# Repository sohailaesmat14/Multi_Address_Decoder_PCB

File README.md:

# Multi Address Decoder PCB

## Description

The Multi-Address Decoder PCB is a versatile printed circuit board designed by Sohaila Esmat using Eagle PCB design software. It serves as a crucial component in digital electronics systems, facilitating the decoding of multiple address lines into individual select signals.

## Features

- **Address Decoding:** Efficiently decodes multiple address lines into select signals.
- **Versatile Design:** Can be integrated into various digital electronics projects requiring address decoding functionality.
- **Customizable:** The design is open for customization and adaptation to specific project requirements.
- **Eagle PCB Design:** Designed using Eagle PCB design software, ensuring reliability and compatibility with industry-standard workflows.

## Design Files

- **Schematic:** The schematic diagram of the Multi-Address Decoder PCB is provided in Eagle `.sch` format.
- **PCB Layout:** The PCB layout design files are available in Eagle `.brd` format.
- **Gerber Files:** Gerber files for manufacturing the PCB are included for easy fabrication.
## PCB Design:

## Usage

1. **Customization:** Modify the design to suit your specific project requirements, such as the number of address lines and select outputs.
2. **Fabrication:** Use the provided Gerber files to manufacture the PCB according to the design specifications.
3. **Integration:** Incorporate the Multi-Address Decoder PCB into your digital electronics project, connecting address lines and select outputs as needed.
4. **Testing:** Validate the functionality of the PCB by testing its address decoding capabilities in your system.

## Author

- **Sohaila Esmat:** [LinkedIn](https://www.linkedin.com/in/sohailaesmat/)

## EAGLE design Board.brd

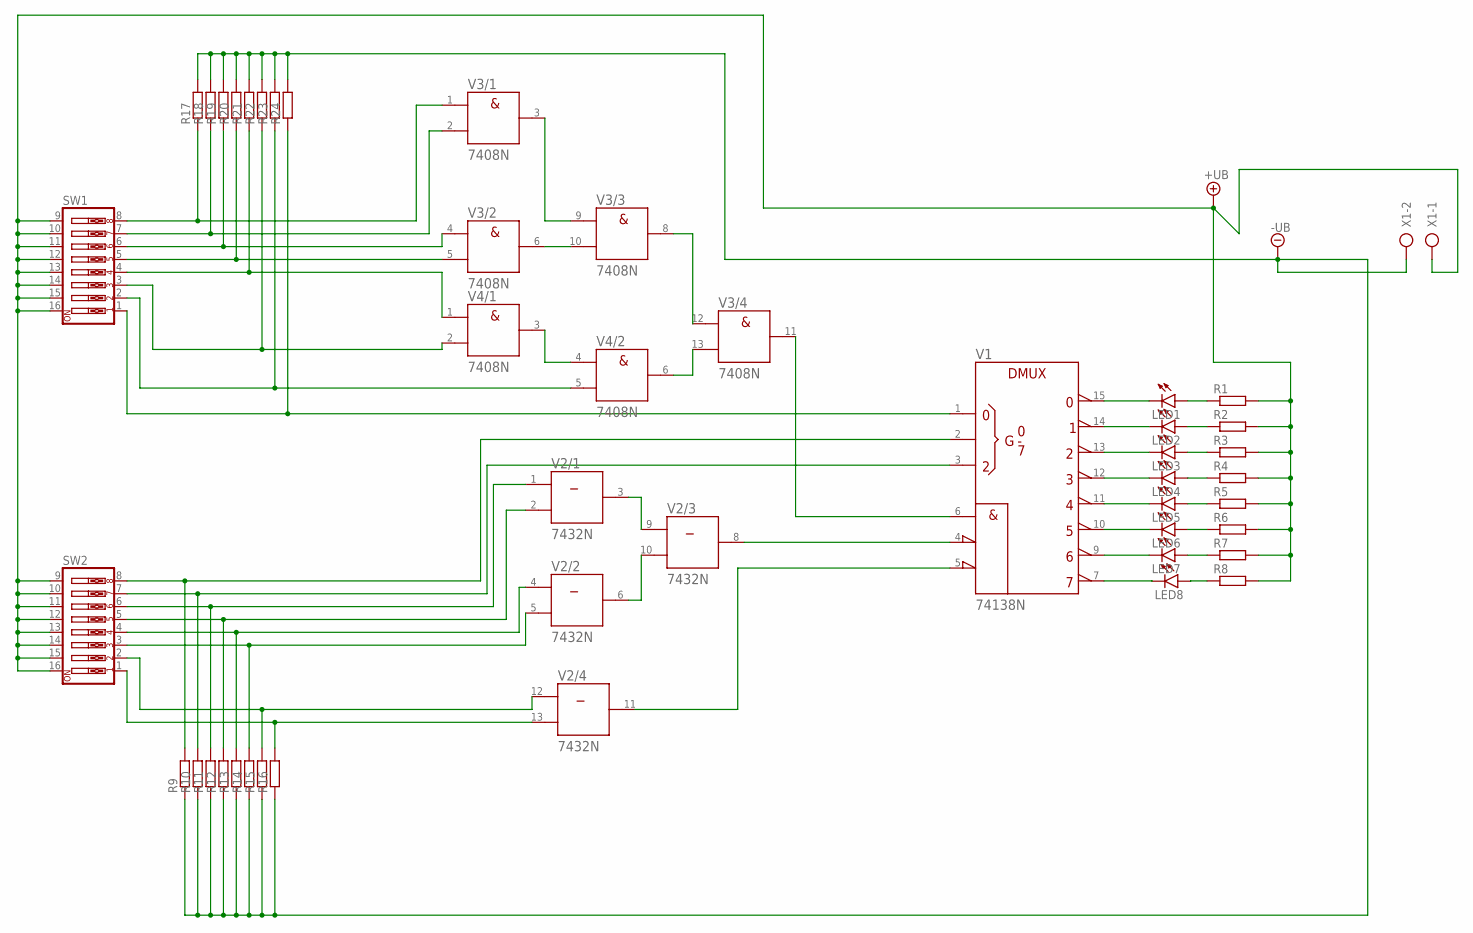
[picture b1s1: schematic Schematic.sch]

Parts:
LED1, LED2, LED3, LED4, LED5, LED6, LED7, LED8: LED5MM
R1, R2, R3, R4, R5, R6, R7, R8, R9, R10, R11, R12, R13, R14, R15, R16, R17, R18, R19, R20, R21, R22, R23, R24: R-EU_0207/10; 0207/10
SW1, SW2: SW_DIP-8; EDG-08
V1: 74138N; DIL16
V2: 7432N; DIL14
V3, V4: 7408N; DIL14
X1: AK500/2

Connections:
+UB: R1.2, R2.2, R3.2, R4.2, R5.2, R6.2, R7.2, R8.2, SW1.9, SW1.10, SW1.11, SW1.12, SW1.13, SW1.14, SW1.15, SW1.16, SW2.9, SW2.10, SW2.11, SW2.12, SW2.13, SW2.14, SW2.15, SW2.16, V1.16 (+UB), V2.14 (+UB), V3.14 (+UB), V4.14 (+UB), X1.1
-UB: R9.1, R10.1, R11.1, R12.1, R13.1, R14.1, R15.1, R16.1, R17.2, R18.2, R19.2, R20.2, R21.2, R22.2, R23.2, R24.2, V1.8 (-UB), V2.7 (-UB), V3.7 (-UB), V4.7 (-UB), X1.2
unnamed: V2.3 (Y), V2.9 (A)
unnamed: V2.6 (Y), V2.10 (B)
unnamed: V1.4 (!G2A), V2.8 (Y)
unnamed: V1.5 (!G2B), V2.11 (Y)
unnamed: V3.3 (Y), V3.9 (A)
unnamed: V3.6 (Y), V3.10 (B)
unnamed: V3.8 (Y), V3.12 (A)
unnamed: V4.3 (Y), V4.4 (A)
unnamed: V3.13 (B), V4.6 (Y)
unnamed: V1.6 (G1), V3.11 (Y)
unnamed: R16.2, SW2.1, V2.13 (B)
unnamed: R15.2, SW2.2, V2.12 (A)
unnamed: R14.2, SW2.3, V2.5 (B)
unnamed: R13.2, SW2.4, V2.4 (A)
unnamed: R12.2, SW2.5, V2.2 (B)
unnamed: R11.2, SW2.6, V2.1 (A)
unnamed: R10.2, SW2.7, V1.3 (C)
unnamed: R9.2, SW2.8, V1.2 (B)
unnamed: R24.1, SW1.1, V1.1 (A)
unnamed: R23.1, SW1.2, V4.5 (B)
unnamed: R22.1, SW1.3, V4.2 (B)
unnamed: R21.1, SW1.4, V4.1 (A)
unnamed: R20.1, SW1.5, V3.5 (B)
unnamed: R19.1, SW1.6, V3.4 (A)
unnamed: R18.1, SW1.7, V3.2 (B)
unnamed: R17.1, SW1.8, V3.1 (A)
unnamed: LED1.K (C), V1.15 (Y0)
unnamed: LED2.K (C), V1.14 (Y1)
unnamed: LED3.K (C), V1.13 (Y2)
unnamed: LED4.K (C), V1.12 (Y3)
unnamed: LED5.K (C), V1.11 (Y4)
unnamed: LED6.K (C), V1.10 (Y5)
unnamed: LED7.K (C), V1.9 (Y6)
unnamed: LED8.K (C), V1.7 (Y7)
unnamed: LED1.A, R1.1
unnamed: LED2.A, R2.1
unnamed: LED3.A, R3.1
unnamed: LED4.A, R4.1
unnamed: LED5.A, R5.1
unnamed: LED6.A, R6.1
unnamed: LED7.A, R7.1
unnamed: LED8.A, R8.1

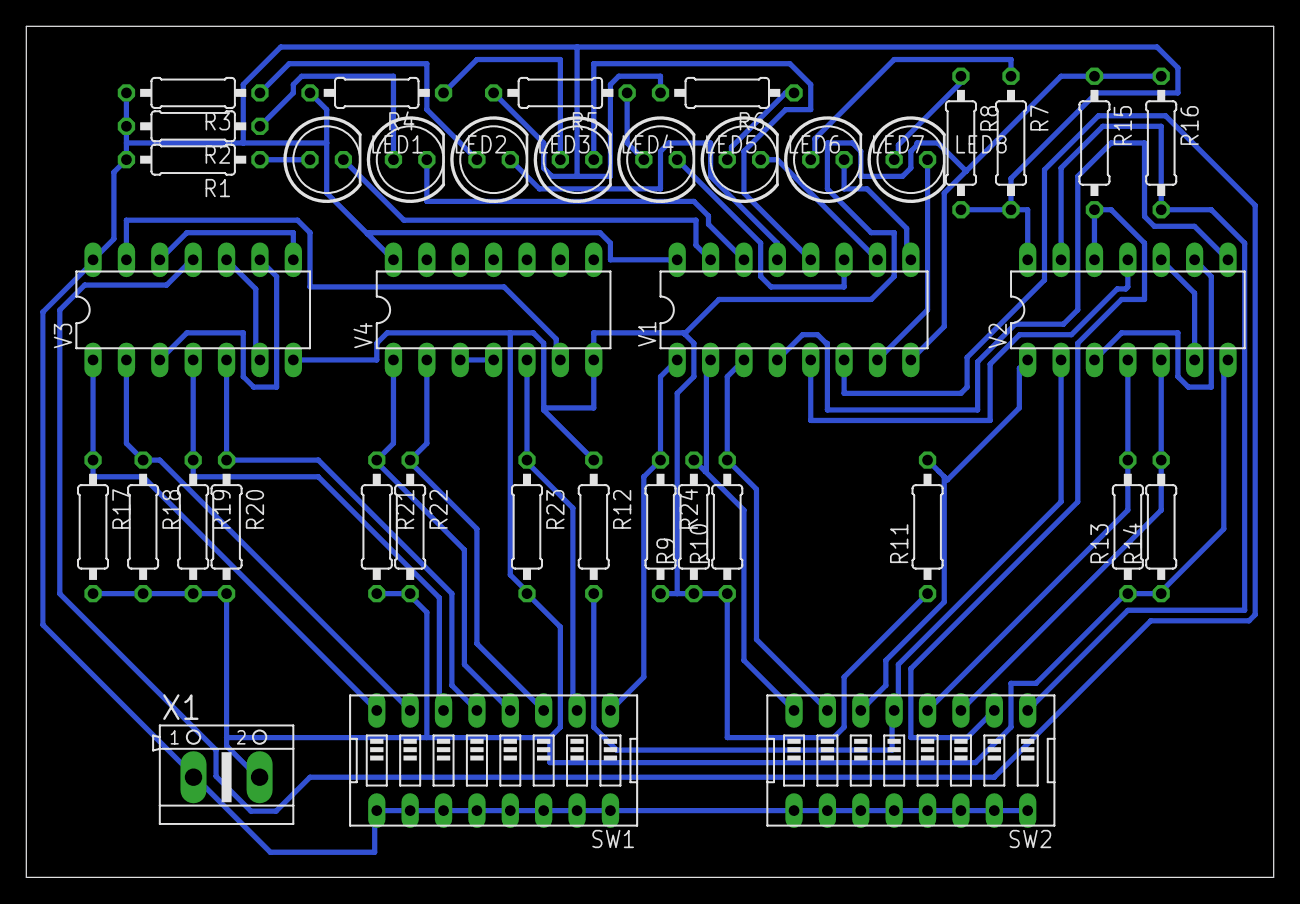
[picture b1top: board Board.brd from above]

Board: 2 copper layers, 94.9 x 64.8 mm, 39 parts (0 on the bottom side), 44 nets.
